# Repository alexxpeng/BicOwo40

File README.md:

# BicOwo40
 Custom 40% keyboard rp2040 (pi pico)

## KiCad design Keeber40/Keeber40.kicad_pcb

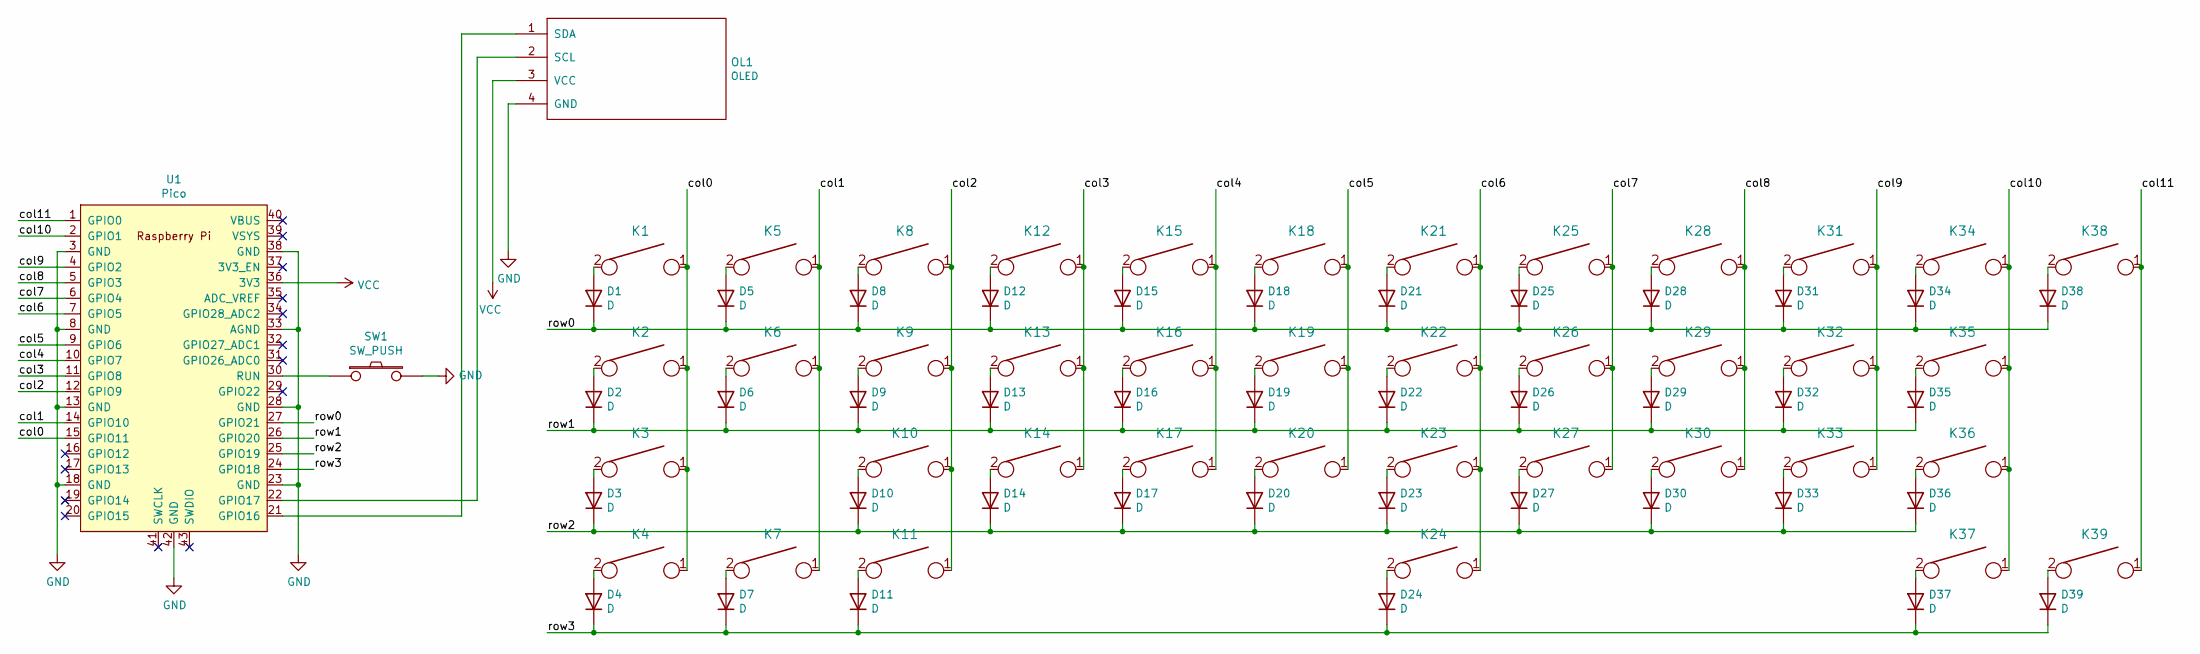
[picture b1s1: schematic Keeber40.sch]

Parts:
D1, D2, D3, D4, D5, D6, D7, D8, D9, D10, D11, D12, D13, D14, D15, D16, D17, D18, D19, D20, D21, D22, D23, D24, D25, D26, D27, D28, D29, D30, D31, D32, D33, D34, D35, D36, D37, D38, D39: D; D_SOD123
K1, K5, K6, K7, K8, K9, K10, K11, K12, K13, K14, K15, K16, K17, K18, K19, K20, K21, K22, K23, K25, K26, K27, K28, K29, K30, K31, K32, K33, K34, K38: KEYSW; Mx_Alps_100
K2, K4, K37, K39: KEYSW; Mx_Alps_125
K3, K35: KEYSW; Mx_Alps_175
K24: KEYSW; Mx_Alps_625
K36: KEYSW; Mx_Alps_225
OL1: OLED; OLED_v2
SW1: SW_PUSH; SW_SPST_TL3342
U1: Pico; RPi_Pico_SMD_TH

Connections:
/col0: K1.1, K2.1, K3.1, K4.1, U1.15 (GPIO11)
/col1: K5.1, K6.1, K7.1, U1.14 (GPIO10)
/col2: K8.1, K9.1, K10.1, K11.1, U1.12 (GPIO9)
/col3: K12.1, K13.1, K14.1, U1.11 (GPIO8)
/col4: K15.1, K16.1, K17.1, U1.10 (GPIO7)
/col5: K18.1, K19.1, K20.1, U1.9 (GPIO6)
/col6: K21.1, K22.1, K23.1, K24.1, U1.7 (GPIO5)
/col7: K25.1, K26.1, K27.1, U1.6 (GPIO4)
/col8: K28.1, K29.1, K30.1, U1.5 (GPIO3)
/col9: K31.1, K32.1, K33.1, U1.4 (GPIO2)
/col10: K34.1, K35.1, K36.1, K37.1, U1.2 (GPIO1)
/col11: K38.1, K39.1, U1.1 (GPIO0)
/row0: D1.1 (K), D5.1 (K), D8.1 (K), D12.1 (K), D15.1 (K), D18.1 (K), D21.1 (K), D25.1 (K), D28.1 (K), D31.1 (K), D34.1 (K), D38.1 (K), U1.27 (GPIO21)
/row1: D2.1 (K), D6.1 (K), D9.1 (K), D13.1 (K), D16.1 (K), D19.1 (K), D22.1 (K), D26.1 (K), D29.1 (K), D32.1 (K), D35.1 (K), U1.26 (GPIO20)
/row2: D3.1 (K), D10.1 (K), D14.1 (K), D17.1 (K), D20.1 (K), D23.1 (K), D27.1 (K), D30.1 (K), D33.1 (K), D36.1 (K), U1.25 (GPIO19)
/row3: D4.1 (K), D7.1 (K), D11.1 (K), D24.1 (K), D37.1 (K), D39.1 (K), U1.24 (GPIO18)
GND: OL1.4 (GND), SW1.2, U1.3 (GND), U1.8 (GND), U1.13 (GND), U1.18 (GND), U1.23 (GND), U1.28 (GND), U1.33 (AGND), U1.38 (GND), U1.42 (GND)
unnamed: D1.2 (A), K1.2
unnamed: D2.2 (A), K2.2
unnamed: D3.2 (A), K3.2
unnamed: D4.2 (A), K4.2
unnamed: D5.2 (A), K5.2
unnamed: D6.2 (A), K6.2
unnamed: D7.2 (A), K7.2
unnamed: D8.2 (A), K8.2
unnamed: D9.2 (A), K9.2
unnamed: D10.2 (A), K10.2
unnamed: D11.2 (A), K11.2
unnamed: D12.2 (A), K12.2
unnamed: D13.2 (A), K13.2
unnamed: D14.2 (A), K14.2
unnamed: D15.2 (A), K15.2
unnamed: D16.2 (A), K16.2
unnamed: D17.2 (A), K17.2
unnamed: D18.2 (A), K18.2
unnamed: D19.2 (A), K19.2
unnamed: D20.2 (A), K20.2
unnamed: D21.2 (A), K21.2
unnamed: D22.2 (A), K22.2
unnamed: D23.2 (A), K23.2
unnamed: D24.2 (A), K24.2
unnamed: D25.2 (A), K25.2
unnamed: D26.2 (A), K26.2
unnamed: D27.2 (A), K27.2
unnamed: D28.2 (A), K28.2
unnamed: D29.2 (A), K29.2
unnamed: D30.2 (A), K30.2
unnamed: D31.2 (A), K31.2
unnamed: D32.2 (A), K32.2
unnamed: D33.2 (A), K33.2
unnamed: D34.2 (A), K34.2
unnamed: D35.2 (A), K35.2
unnamed: D36.2 (A), K36.2
unnamed: D37.2 (A), K37.2
unnamed: D38.2 (A), K38.2
unnamed: D39.2 (A), K39.2
unnamed: OL1.1 (SDA), U1.21 (GPIO16)
unnamed: OL1.2 (SCL), U1.22 (GPIO17)
unnamed: SW1.1, U1.30 (RUN)
VCC: OL1.3 (VCC), U1.36 (3V3)

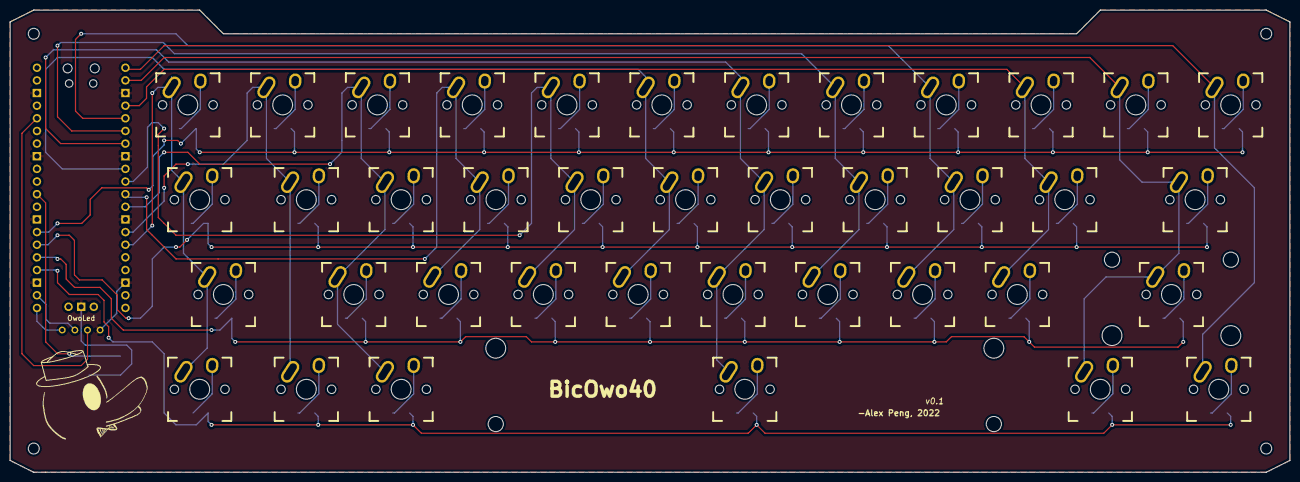
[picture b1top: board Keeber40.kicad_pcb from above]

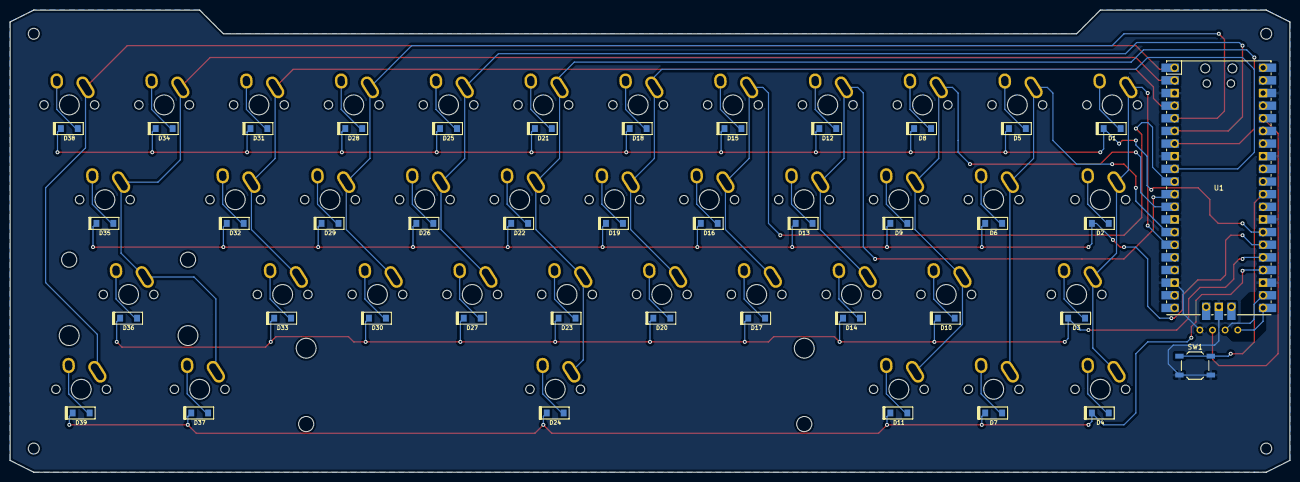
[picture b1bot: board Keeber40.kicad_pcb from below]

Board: 2 copper layers, 257.1 x 92.9 mm, 85 parts (41 on the bottom side), 60 nets.

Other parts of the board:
M2, M2#2, M2#3, M2#4: MountingHole_2.2mm_M2

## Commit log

2022-04-01 KMK firmware
    add firmware python script for pico, compatible with circuit python
2022-04-16 fixed pcb oled traces
2022-04-16 updated keybindings and oled
